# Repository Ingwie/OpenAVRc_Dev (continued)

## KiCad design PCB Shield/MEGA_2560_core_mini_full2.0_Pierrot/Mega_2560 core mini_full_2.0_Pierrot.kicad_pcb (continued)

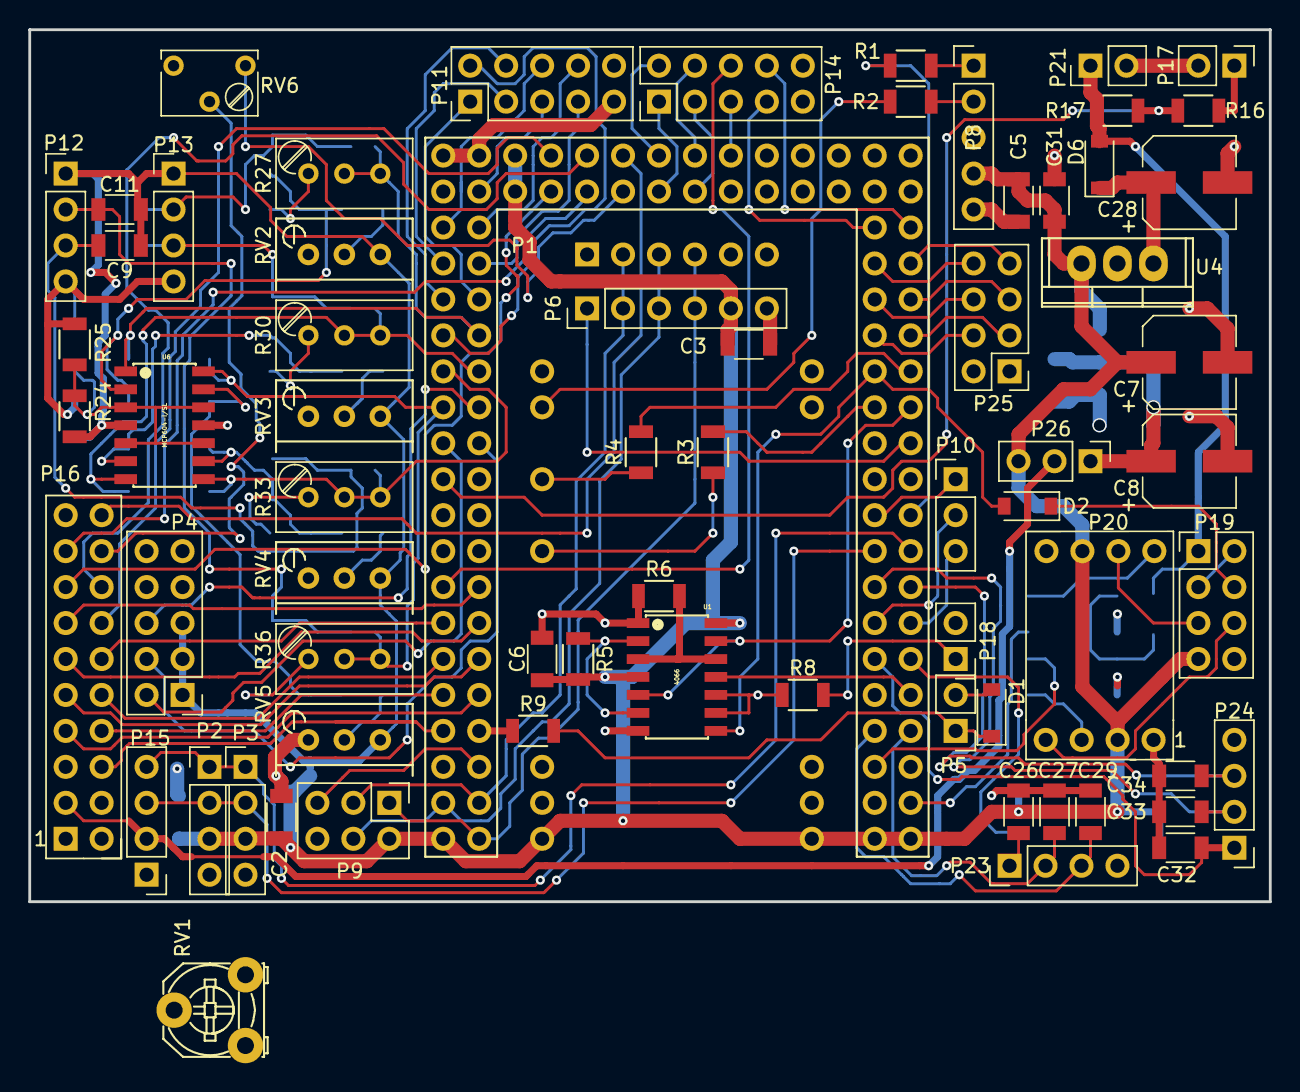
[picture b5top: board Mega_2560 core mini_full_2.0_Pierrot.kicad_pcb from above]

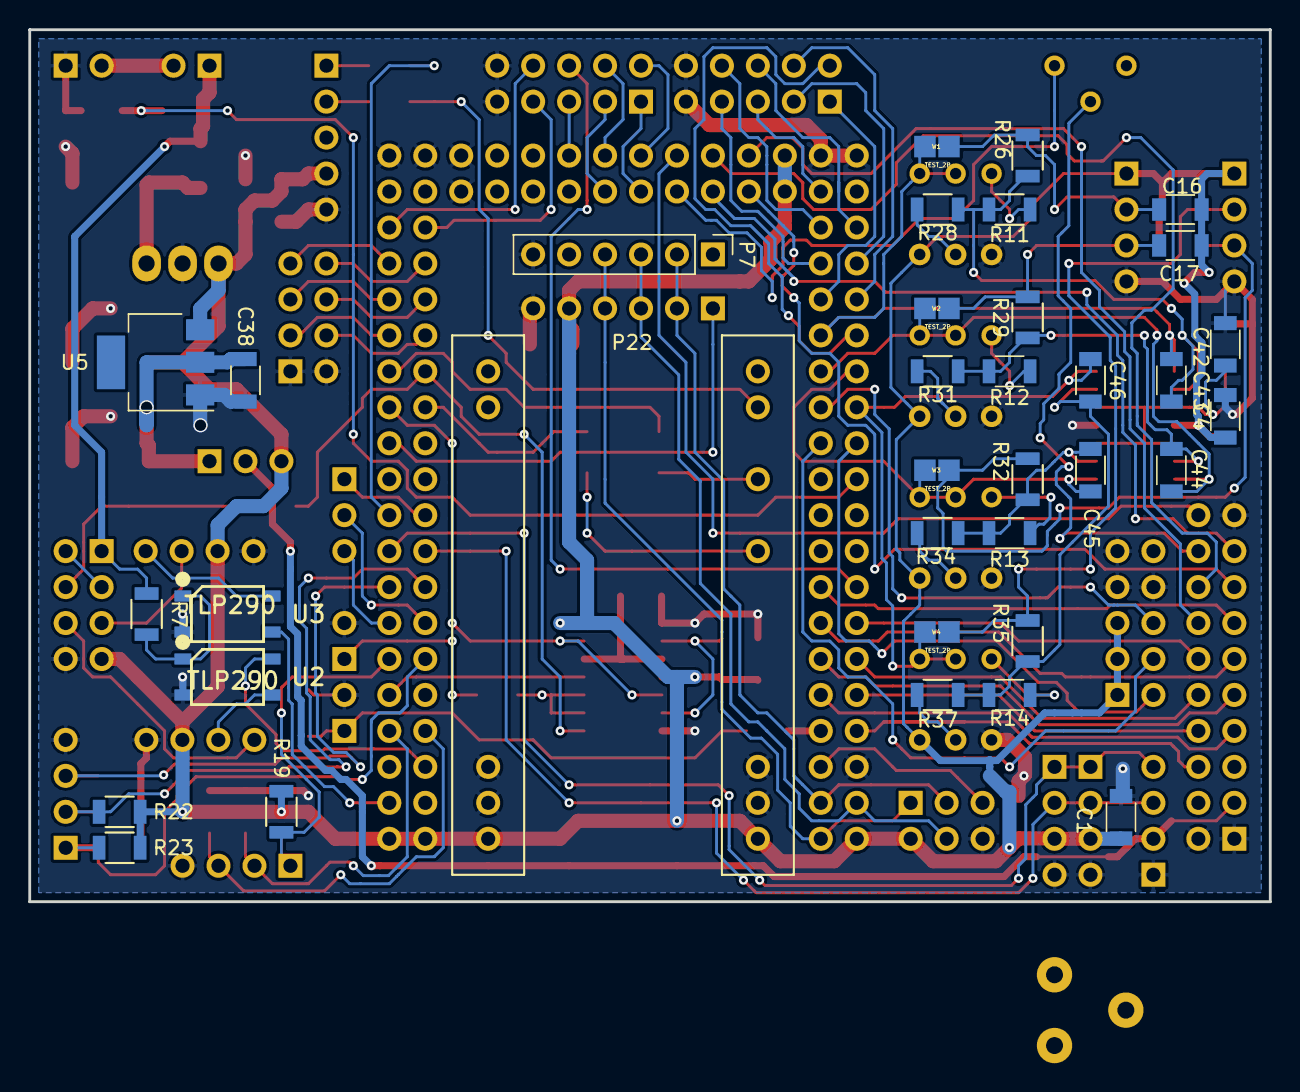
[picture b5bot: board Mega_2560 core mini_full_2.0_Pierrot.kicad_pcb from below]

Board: 2 copper layers, 87.6 x 61.6 mm, 103 parts (35 on the bottom side), 113 nets.

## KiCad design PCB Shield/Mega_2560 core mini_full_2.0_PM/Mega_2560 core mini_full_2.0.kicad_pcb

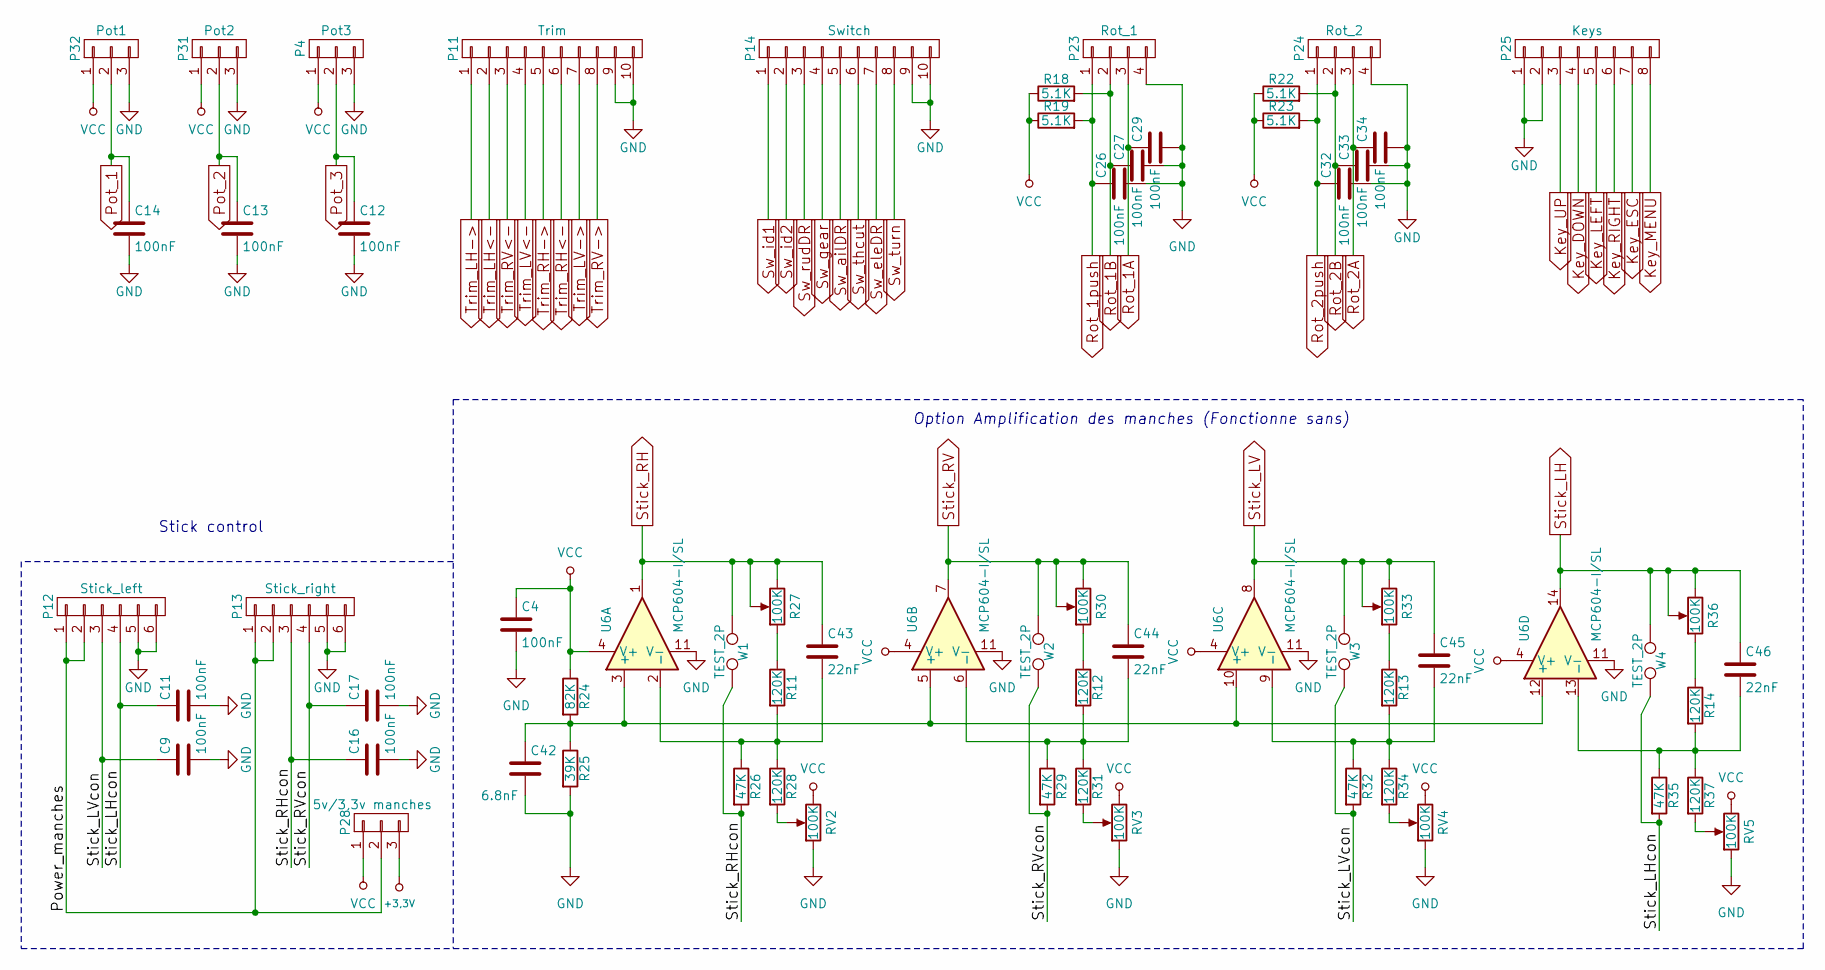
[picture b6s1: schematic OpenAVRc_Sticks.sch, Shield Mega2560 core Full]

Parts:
C4, C9, C11, C12, C13, C14, C16, C17, C26, C27, C29, C32, C33, C34: 100nF; C_1206
C42: 6.8nF; C_1206
C43, C44, C45, C46: 22nF; C_1206
P4: Pot3; Pin_Header_Straight_1x03_Pitch2.54mm
P11: Trim; Pin_Header_Straight_2x05_Pitch2.54mm
P12: Stick_left; Pin_Header_Straight_2x03_Pitch2.54mm
P13: Stick_right; Pin_Header_Straight_1x06_Pitch2.54mm
P14: Switch; Pin_Header_Straight_2x05_Pitch2.54mm
P23: Rot_1; Pin_Header_Straight_1x04_Pitch2.54mm
P24: Rot_2; Pin_Header_Straight_1x04_Pitch2.54mm
P25: Keys; Pin_Header_Straight_2x04_Pitch2.54mm
P28: 5v/3,3v manches; Pin_Header_Straight_1x03_Pitch2.54mm
P31: Pot2; Pin_Header_Straight_1x03_Pitch2.54mm
P32: Pot1; Pin_Header_Straight_1x03_Pitch2.54mm
R11, R12, R13, R14, R28, R31, R34, R37: 120K; R_1206
R18, R19, R22, R23: 5.1K; R_1206
R24: 82K; R_1206
R25: 39K; R_1206
R26, R29, R32, R35: 47K; R_1206
R27, R30, R33, R36: 100K; Potentiometer_Trimmer_Bourns_3296W
RV2, RV3, RV4, RV5: 100K; Potentiometer_Bourns_3296W_3-8Zoll_Inline_ScrewUp
U6: MCP604-I/SL; SOP14
W1, W2, W3, W4: TEST_2P; TESTPT

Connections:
+3.3V: P28.3; also elsewhere on the board
/OpenAVRc_Sticks/Power_manches: P12.1, P12.2, P13.1, P13.2, P28.2
/OpenAVRc_Sticks/Stick_LHcon: C11.1, P12.4, R35.2, W4.2
/OpenAVRc_Sticks/Stick_LVcon: C9.1, P12.3, R32.2, W3.2
/OpenAVRc_Sticks/Stick_RHcon: C16.1, P13.3, R26.2, W1.2
/OpenAVRc_Sticks/Stick_RVcon: C17.1, P13.4, R29.2, W2.2
GND: C4.2, C9.2, C11.2, C12.2, C13.2, C14.2, C16.2, C17.2, C26.2, C27.2, C29.2, C32.2, C33.2, C34.2, C42.2, P4.3, P11.9, P11.10, P12.5, P12.6, P13.5, P13.6, P14.9, P14.10, P23.4, P24.4, P25.1, P25.2, P31.3, P32.3, R25.2, RV2.1, RV3.1, RV4.1, RV5.1, U6.11 (V-); also elsewhere on the board
Key_DOWN: P25.4; also elsewhere on the board
Key_ESC: P25.7; also elsewhere on the board
Key_LEFT: P25.5; also elsewhere on the board
Key_MENU: P25.8; also elsewhere on the board
Key_RIGHT: P25.6; also elsewhere on the board
Key_UP: P25.3; also elsewhere on the board
unnamed: C42.1, R24.2, R25.1, U6.3 (+), U6.5 (+), U6.10 (+), U6.12 (+)
unnamed: C43.2, R11.2, R26.1, R28.1, U6.2 (-)
unnamed: C44.2, R12.2, R29.1, R31.1, U6.6 (-)
unnamed: C45.2, R13.2, R32.1, R34.1, U6.9 (-)
unnamed: C46.2, R14.2, R35.1, R37.1, U6.13 (-)
unnamed: R11.1, R27.1
unnamed: R12.1, R30.1
unnamed: R13.1, R33.1
unnamed: R14.1, R36.1
unnamed: R28.2, RV2.2
unnamed: R31.2, RV3.2
unnamed: R34.2, RV4.2
unnamed: R37.2, RV5.2
Pot_1: C14.1, P32.2; also elsewhere on the board
Pot_2: C13.1, P31.2; also elsewhere on the board
Pot_3: C12.1, P4.2; also elsewhere on the board
Rot_1A: C29.1, P23.3; also elsewhere on the board
Rot_1B: C27.1, P23.2, R18.2; also elsewhere on the board
Rot_1push: C26.1, P23.1, R19.2; also elsewhere on the board
Rot_2A: C34.1, P24.3; also elsewhere on the board
Rot_2B: C33.1, P24.2, R22.2; also elsewhere on the board
Rot_2push: C32.1, P24.1, R23.2; also elsewhere on the board
Stick_LH: C46.1, R36.2, R36.3, U6.14, W4.1; also elsewhere on the board
Stick_LV: C45.1, R33.2, R33.3, U6.8, W3.1; also elsewhere on the board
Stick_RH: C43.1, R27.2, R27.3, U6.1, W1.1; also elsewhere on the board
Stick_RV: C44.1, R30.2, R30.3, U6.7, W2.1; also elsewhere on the board
Sw_ailDR: P14.5; also elsewhere on the board
Sw_eleDR: P14.7; also elsewhere on the board
Sw_gear: P14.4; also elsewhere on the board
Sw_id1: P14.1; also elsewhere on the board
Sw_id2: P14.2; also elsewhere on the board
Sw_rudDR: P14.3; also elsewhere on the board
Sw_thcut: P14.6; also elsewhere on the board
Sw_turn: P14.8; also elsewhere on the board
Trim_LH->: P11.1; also elsewhere on the board
Trim_LH<-: P11.2; also elsewhere on the board
Trim_LV->: P11.7; also elsewhere on the board
Trim_LV<-: P11.4; also elsewhere on the board
Trim_RH->: P11.5; also elsewhere on the board
Trim_RH<-: P11.6; also elsewhere on the board
Trim_RV->: P11.8; also elsewhere on the board
Trim_RV<-: P11.3; also elsewhere on the board
VCC: C4.1, P4.1, P28.1, P31.1, P32.1, R18.1, R19.1, R22.1, R23.1, R24.1, RV2.3, RV3.3, RV4.3, RV5.3, U6.4 (V+); also elsewhere on the board

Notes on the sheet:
Stick control
Option Amplification des manches (Fonctionne sans)

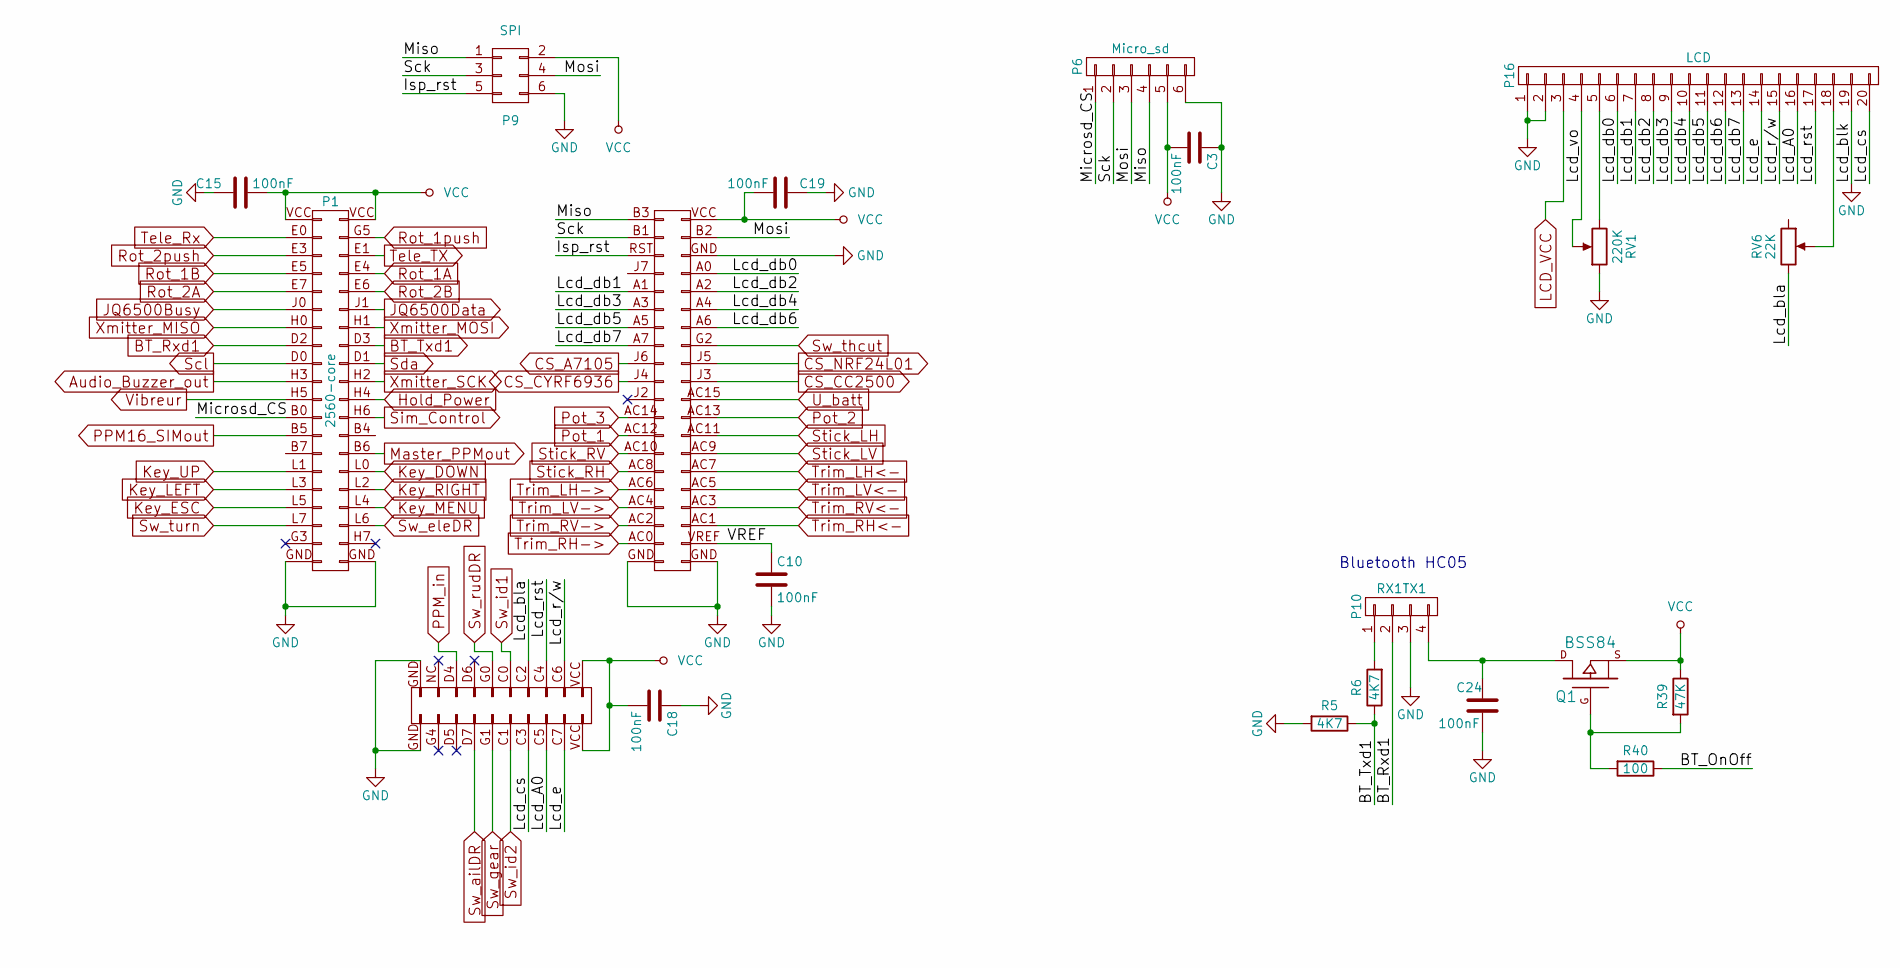
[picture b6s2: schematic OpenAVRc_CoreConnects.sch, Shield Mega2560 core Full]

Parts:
C3, C10, C15, C18, C19, C24: 100nF; C_1206
P1: 2560-core; Connectors-2560-core
P6: Micro_sd; Pin_Header_Straight_1x06_Pitch2.54mm
P9: SPI; Pin_Header_Straight_2x03_Pitch2.54mm
P10: RX1TX1; Pin_Header_Straight_1x04_Pitch2.54mm
P16: LCD; Pin_Header_Straight_2x10_Pitch2.54mm
Q1: BSS84
R5, R6: 4K7; R_1206
R39: 47K; R_1206
R40: 100; R_1206
RV1: 220K; Potentiometer_Trimmer_Bourns_3296W
RV6: 22K; Potentiometer_Trimmer_Bourns_3296W

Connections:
/OpenAVRc_CoreConnects/Isp_rst: P1.RST (P75), P9.5
/OpenAVRc_CoreConnects/Lcd_A0: P1.C5 (P85), P16.16
/OpenAVRc_CoreConnects/Lcd_bla: P1.C2 (P88), RV6.3
/OpenAVRc_CoreConnects/Lcd_cs: P1.C3 (P87), P16.20
/OpenAVRc_CoreConnects/Lcd_db0: P1.A0 (P74), P16.6
/OpenAVRc_CoreConnects/Lcd_db1: P1.A1 (P71), P16.7
/OpenAVRc_CoreConnects/Lcd_db2: P1.A2 (P72), P16.8
/OpenAVRc_CoreConnects/Lcd_db3: P1.A3 (P69), P16.9
/OpenAVRc_CoreConnects/Lcd_db4: P1.A4 (P70), P16.10
/OpenAVRc_CoreConnects/Lcd_db5: P1.A5 (P67), P16.11
/OpenAVRc_CoreConnects/Lcd_db6: P1.A6 (P68), P16.12
/OpenAVRc_CoreConnects/Lcd_db7: P1.A7 (P65), P16.13
/OpenAVRc_CoreConnects/Lcd_e: P1.C7 (P83), P16.14
/OpenAVRc_CoreConnects/Lcd_r/w: P1.C6 (P84), P16.15
/OpenAVRc_CoreConnects/Lcd_rst: P1.C4 (P86), P16.17
/OpenAVRc_CoreConnects/Lcd_vo: P16.4, RV1.2
/OpenAVRc_CoreConnects/Microsd_CS: P1.B0 (P24), P6.1
/OpenAVRc_CoreConnects/Miso: P1.B3 (P79), P6.4, P9.1
/OpenAVRc_CoreConnects/Mosi: P1.B2 (P78), P6.3, P9.4
/OpenAVRc_CoreConnects/Sck: P1.B1 (P77), P6.2, P9.3
/OpenAVRc_CoreConnects/VREF: C10.1, P1.VREF (P44)
Audio_Buzzer_out: P1.H3 (P20); also elsewhere on the board
BT_Rxd1: P1.D2 (P16), P10.2
BT_Txd1: P1.D3 (P15), R5.1, R6.1
CS_A7105: P1.J6 (P63); also elsewhere on the board
CS_CC2500: P1.J3 (P62); also elsewhere on the board
CS_CYRF6936: P1.J4 (P61); also elsewhere on the board
CS_NRF24L01: P1.J5 (P64); also elsewhere on the board
GND: C3.1, C10.2, C15.1, C18.1, C19.1, C24.2, P1.GND (P100), P6.6, P9.6, P10.3, P16.1, P16.2, P16.19, R5.2, RV1.1; also elsewhere on the board
Hold_Power: P1.H4 (P21); also elsewhere on the board
JQ6500Busy: P1.J0 (P12); also elsewhere on the board
JQ6500Data: P1.J1 (P11); also elsewhere on the board
Key_DOWN: P1.L0 (P29); also elsewhere on the board
Key_ESC: P1.L5 (P34); also elsewhere on the board
Key_LEFT: P1.L3 (P32); also elsewhere on the board
Key_MENU: P1.L4 (P33); also elsewhere on the board
Key_RIGHT: P1.L2 (P31); also elsewhere on the board
Key_UP: P1.L1 (P30); also elsewhere on the board
LCD_VCC: P16.3; also elsewhere on the board
Master_PPMout: P1.B6 (P27); also elsewhere on the board
unnamed: C24.1, P10.4, Q1.D
unnamed: P10.1, R6.2
unnamed: P16.5, RV1.3
unnamed: P16.18, RV6.2
unnamed: Q1.G, R39.2, R40.2
PPM16_SIMout: P1.B5 (P26); also elsewhere on the board
PPM_in: P1.D4 (P96); also elsewhere on the board
Pot_1: P1.AC12 (P55); also elsewhere on the board
Pot_2: P1.AC13 (P58); also elsewhere on the board
Pot_3: P1.AC14 (P57); also elsewhere on the board
Rot_1A: P1.E4 (P7); also elsewhere on the board
Rot_1B: P1.E5 (P8); also elsewhere on the board
Rot_1push: P1.G5 (P3); also elsewhere on the board
Rot_2A: P1.E7 (P10); also elsewhere on the board
Rot_2B: P1.E6 (P9); also elsewhere on the board
Rot_2push: P1.E3 (P6); also elsewhere on the board
Scl: P1.D0 (P18); also elsewhere on the board
Sda: P1.D1 (P17); also elsewhere on the board
Sim_Control: P1.H6 (P23); also elsewhere on the board
Stick_LH: P1.AC11 (P56); also elsewhere on the board
Stick_LV: P1.AC9 (P54); also elsewhere on the board
Stick_RH: P1.AC8 (P51); also elsewhere on the board
Stick_RV: P1.AC10 (P53); also elsewhere on the board
Sw_ailDR: P1.D7 (P93); also elsewhere on the board
Sw_eleDR: P1.L6 (P35); also elsewhere on the board
Sw_gear: P1.G1 (P91); also elsewhere on the board
Sw_id1: P1.C0 (P90); also elsewhere on the board
Sw_id2: P1.C1 (P89); also elsewhere on the board
Sw_rudDR: P1.G0 (P92); also elsewhere on the board
Sw_thcut: P1.G2 (P66); also elsewhere on the board
Sw_turn: P1.L7 (P36); also elsewhere on the board
Tele_RX: P1.E0 (P4); also elsewhere on the board
Tele_TX: P1.E1 (P5); also elsewhere on the board
Trim_LH->: P1.AC6 (P49); also elsewhere on the board
Trim_LH<-: P1.AC7 (P52); also elsewhere on the board
Trim_LV->: P1.AC4 (P47); also elsewhere on the board
Trim_LV<-: P1.AC5 (P50); also elsewhere on the board
Trim_RH->: P1.AC0 (P43); also elsewhere on the board
Trim_RH<-: P1.AC1 (P46); also elsewhere on the board
Trim_RV->: P1.AC2 (P45); also elsewhere on the board
Trim_RV<-: P1.AC3 (P48); also elsewhere on the board
U_batt: P1.AC15 (P60); also elsewhere on the board
VCC: C3.2, C15.2, C18.2, C19.2, P1.VCC (P1), P6.5, P9.2, Q1.S, R39.1; also elsewhere on the board
Vibreur: P1.H5 (P22); also elsewhere on the board
Xmitter_MISO: P1.H0 (P14); also elsewhere on the board
Xmitter_MOSI: P1.H1 (P13); also elsewhere on the board
Xmitter_SCK: P1.H2 (P19); also elsewhere on the board

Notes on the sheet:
Bluetooth HC05

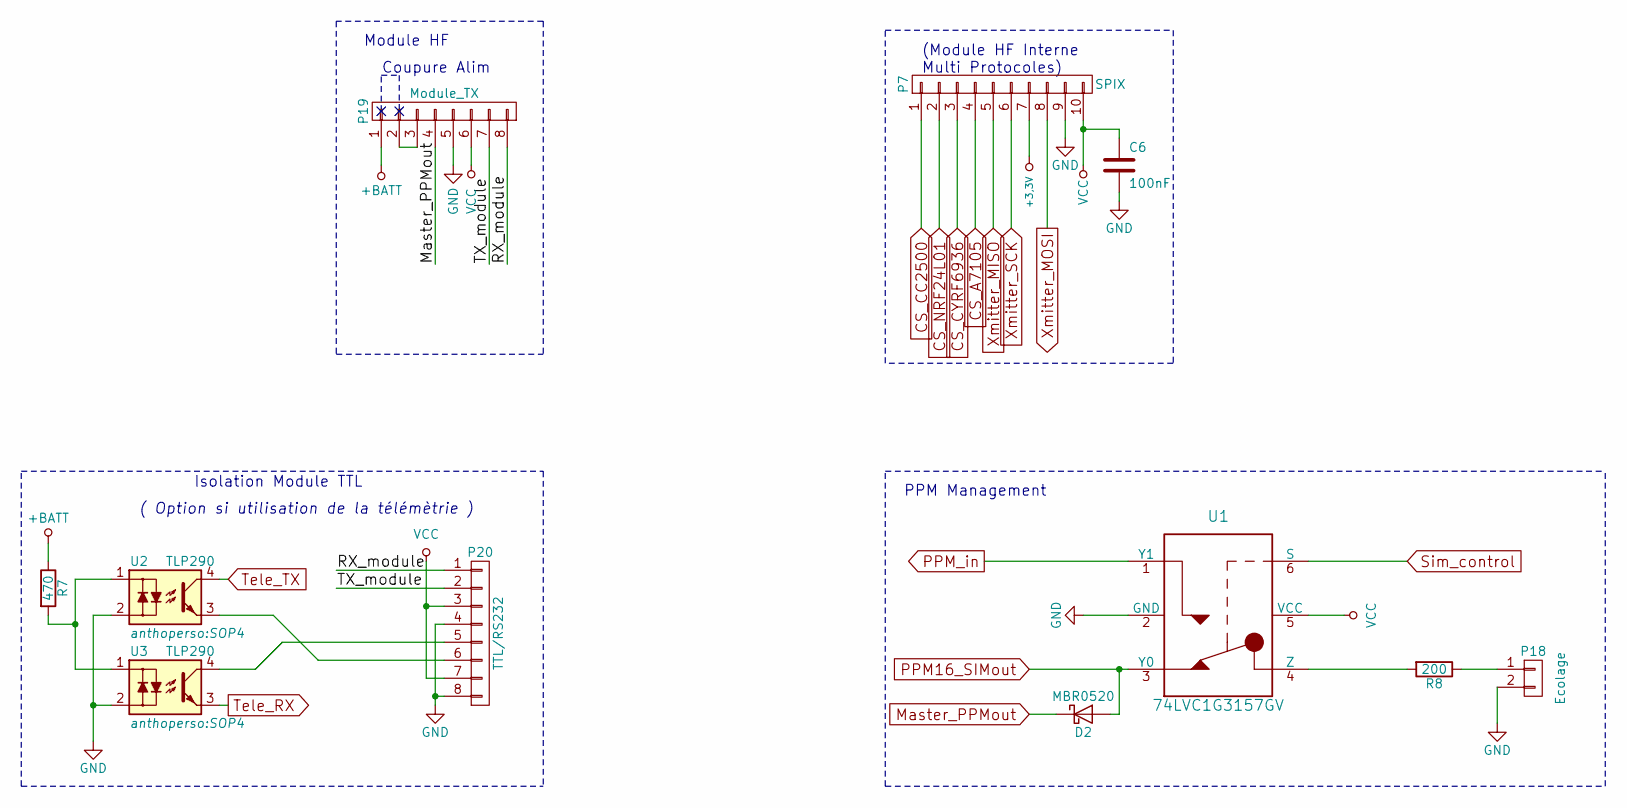
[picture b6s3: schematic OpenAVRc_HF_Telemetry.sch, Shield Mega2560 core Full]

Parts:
C6: 100nF; C_1206
D2: MBR0520; D_SOD-123
P7: SPIX; Pin_Header_Straight_2x05_Pitch2.54mm
P18: Ecolage; Pin_Header_Straight_1x02_Pitch2.54mm
P19: Module_TX; Pin_Header_Straight_2x04_Pitch2.54mm
P20: TTL/RS232; Con_RS232_TTL
R7: 470; R_1206
R8: 200; R_1206
U1: 74LVC1G3157GV; SOT-457
U2, U3: TLP290; SOP4

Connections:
+3.3V: P7.7; also elsewhere on the board
+BATT: P19.1, R7.1; also elsewhere on the board
/OpenAVRc_HF_Telemetry/RX_module: P19.8, P20.1
/OpenAVRc_HF_Telemetry/TX_module: P19.7, P20.2
CS_A7105: P7.4; also elsewhere on the board
CS_CC2500: P7.1; also elsewhere on the board
CS_CYRF6936: P7.3; also elsewhere on the board
CS_NRF24L01: P7.2; also elsewhere on the board
GND: C6.2, P7.9, P18.2, P19.5, P20.4, P20.8, U1.2 (GND), U2.2, U3.2; also elsewhere on the board
Master_PPMout: D2.1 (K), P19.4; also elsewhere on the board
unnamed: P18.1, R8.1
unnamed: P19.2, P19.3
unnamed: P20.5, U3.4
unnamed: P20.6, U2.3
unnamed: R7.2, U2.1, U3.1
unnamed: R8.2, U1.4 (Z)
PPM16_SIMout: D2.2 (A), U1.3 (Y0); also elsewhere on the board
PPM_in: U1.1 (Y1); also elsewhere on the board
Sim_Control: U1.6 (S); also elsewhere on the board
Tele_RX: U3.3; also elsewhere on the board
Tele_TX: U2.4; also elsewhere on the board
VCC: C6.1, P7.10, P19.6, P20.3, P20.7, U1.5 (VCC); also elsewhere on the board
Xmitter_MISO: P7.5; also elsewhere on the board
Xmitter_MOSI: P7.8; also elsewhere on the board
Xmitter_SCK: P7.6; also elsewhere on the board

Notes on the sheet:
Isolation Module TTL
PPM Management
( Option si utilisation de la télémètrie )
Coupure Alim
Module HF
(Module HF Interne Multi Protocoles)

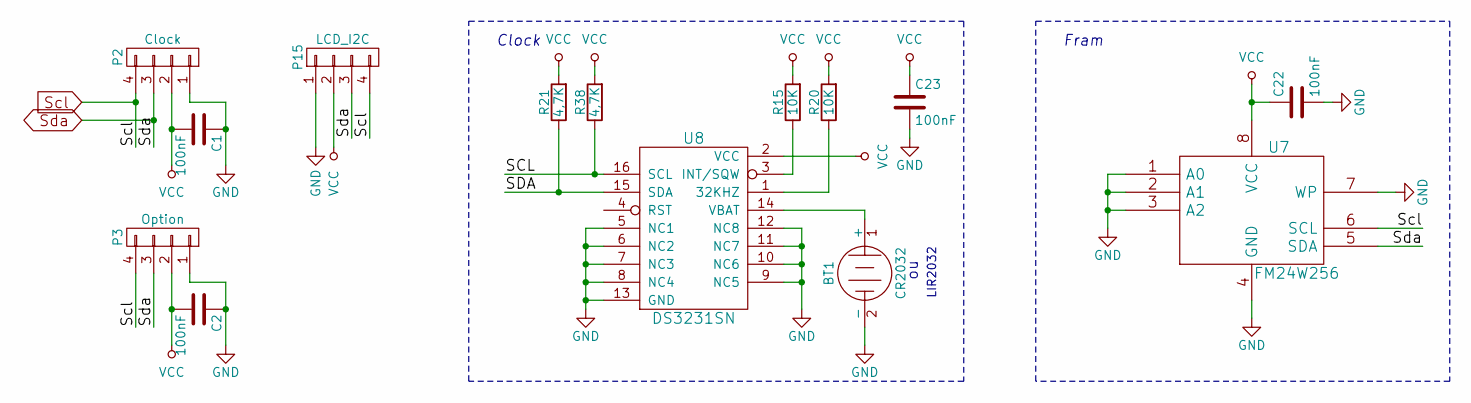
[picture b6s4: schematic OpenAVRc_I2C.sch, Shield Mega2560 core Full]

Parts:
BT1: CR2032; Pin_Header_Straight_1x02_Pitch2.54mm
C1, C2, C22, C23: 100nF; C_1206
P2: Clock; Pin_Header_Straight_1x04_Pitch2.54mm
P3: Option; Pin_Header_Straight_1x04_Pitch2.54mm
P15: LCD_I2C; Pin_Header_Straight_1x04_Pitch2.54mm
R15, R20: 10K; R_1206
R21, R38: 4,7K; R_1206
U7: FM24W256; SOIC-8-FRAM_DI
U8: DS3231SN; SO-16-DS3231

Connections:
GND: BT1.2 (-), C1.1, C2.1, C22.2, C23.2, P2.1, P3.1, P15.1, U7.1 (A0), U7.2 (A1), U7.3 (A2), U7.4 (GND), U7.7 (WP), U8.5 (NC1), U8.6 (NC2), U8.7 (NC3), U8.8 (NC4), U8.9 (NC5), U8.10 (NC6), U8.11 (NC7), U8.12 (NC8), U8.13 (GND); also elsewhere on the board
unnamed: BT1.1 (+), U8.14 (VBAT)
unnamed: R15.1, U8.3 (INT/SQW)
unnamed: R20.1, U8.1 (32KHZ)
Scl: P2.4, P3.4, P15.4, R38.1, U7.6 (SCL), U8.16 (SCL); also elsewhere on the board
Sda: P2.3, P3.3, P15.3, R21.1, U7.5 (SDA), U8.15 (SDA); also elsewhere on the board
VCC: C1.2, C2.2, C22.1, C23.1, P2.2, P3.2, P15.2, R15.2, R20.2, R21.2, R38.2, U7.8 (VCC), U8.2 (VCC); also elsewhere on the board

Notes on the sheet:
Clock
Fram
LIR2032

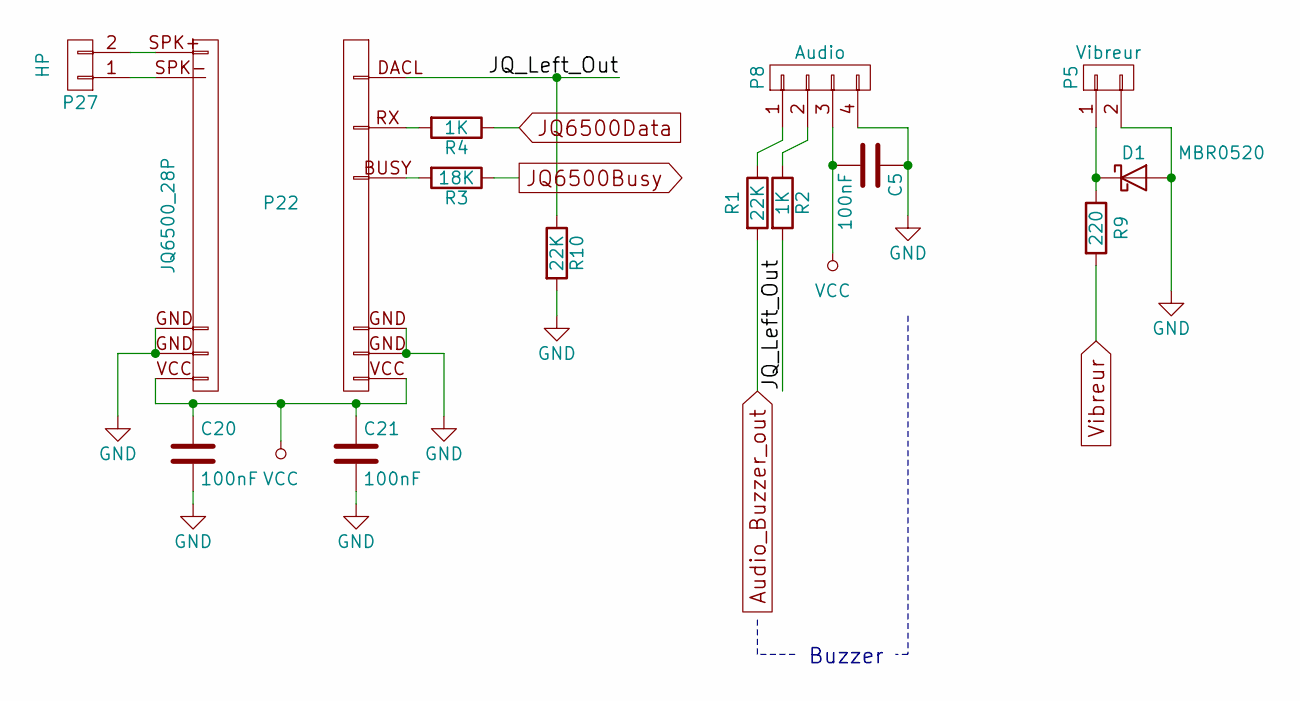
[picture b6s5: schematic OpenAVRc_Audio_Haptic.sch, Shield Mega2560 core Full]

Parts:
C5, C20, C21: 100nF; C_1206
D1: MBR0520; D_SOD-123
P5: Vibreur; Pin_Header_Straight_1x02_Pitch2.54mm
P8: Audio; Pin_Header_Straight_1x04_Pitch2.54mm
P22: JQ6500_28P; connector_mini-JQ6500-28P
P27: HP; Pin_Header_Straight_1x02_Pitch2.54mm
R1, R10: 22K; R_1206
R2, R4: 1K; R_1206
R3: 18K; R_1206
R9: 220; R_1206

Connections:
/OpenAVRc_Audio_Haptic/JQ_Left_Out: P22.DACL (P16), R2.2, R10.1
Audio_Buzzer_out: R1.2; also elsewhere on the board
GND: C5.1, C20.2, C21.2, D1.2 (A), P5.2, P8.4, P22.GND (P12), R10.2; also elsewhere on the board
JQ6500Busy: R3.1; also elsewhere on the board
JQ6500Data: R4.1; also elsewhere on the board
unnamed: D1.1 (K), P5.1, R9.1
unnamed: P8.1, R1.1
unnamed: P8.2, R2.1
unnamed: P22.BUSY (P20), R3.2
unnamed: P22.RX (P18), R4.2
unnamed: P22.SPK+ (P1), P27.2
unnamed: P22.SPK- (P2), P27.1
VCC: C5.2, C20.1, C21.1, P8.3, P22.VCC (P14); also elsewhere on the board
Vibreur: R9.2; also elsewhere on the board

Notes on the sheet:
Buzzer

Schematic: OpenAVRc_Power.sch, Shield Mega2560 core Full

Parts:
C7, C28: 100µF; CP_Elec_6.3x5.3
C8: 47µF; CP_Elec_6.3x5.3
C31, C38: 100nF; C_1206
D3, D4: LL4148; D_SCD80_HandSoldering
D6: MBR0520; D_SOD-123
P17: BATT; Pin_Header_Straight_1x02_Pitch2.54mm
P21: Sw_power; Pin_Header_Straight_1x02_Pitch2.54mm
P26: LCD_Alim; Pin_Header_Straight_1x03_Pitch2.54mm
P29: Sw_On; Pin_Header_Straight_1x02_Pitch2.54mm
P30: MiniDCDC3A
R16: 2.7K; R_1206
R17: 5.1K; R_1206
R41: 33K; R_1206
R42: 2.2K; R_1206
R43: 10K; R_1206
U4: PM5033; PM5033_SIL5
U5: LD1117S33TR; SOT-223

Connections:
+3.3V: C8.1, C38.1, P26.3, U4.5 (3V3), U5.2 (VO1), U5.4 (VO2); also elsewhere on the board
+BATT: D6.2 (A), P21.2, R17.2; also elsewhere on the board
/OpenAVRc_Power/DCDC_IN+: C28.1, D6.1 (K), P30.3, P30.4, R41.1, U4.2 (VIN)
/OpenAVRc_Power/LIPO+: P17.2, P21.1
GND: C7.2, C8.2, C28.2, C31.2, C38.2, P17.1, P30.1, P30.2, P30.7, P30.8, R16.2, R43.2, U4.3 (GND), U5.1 (GND); also elsewhere on the board
Hold_Power: R42.2; also elsewhere on the board
LCD_VCC: P26.2; also elsewhere on the board
unnamed: P29.1, R41.2
unnamed: P29.2, R42.1, R43.1, U4.1 (EN)
U_batt: R16.1, R17.1; also elsewhere on the board
VCC: C7.1, C31.1, P26.1, P30.5, P30.6, U4.4 (5V), U5.3 (VI); also elsewhere on the board

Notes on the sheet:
+3.3V
+5V
Power Management
Option si utilisation du 3.3V dans le montage
Power Switch
DCDC_IN-
Option module DCDC 3A

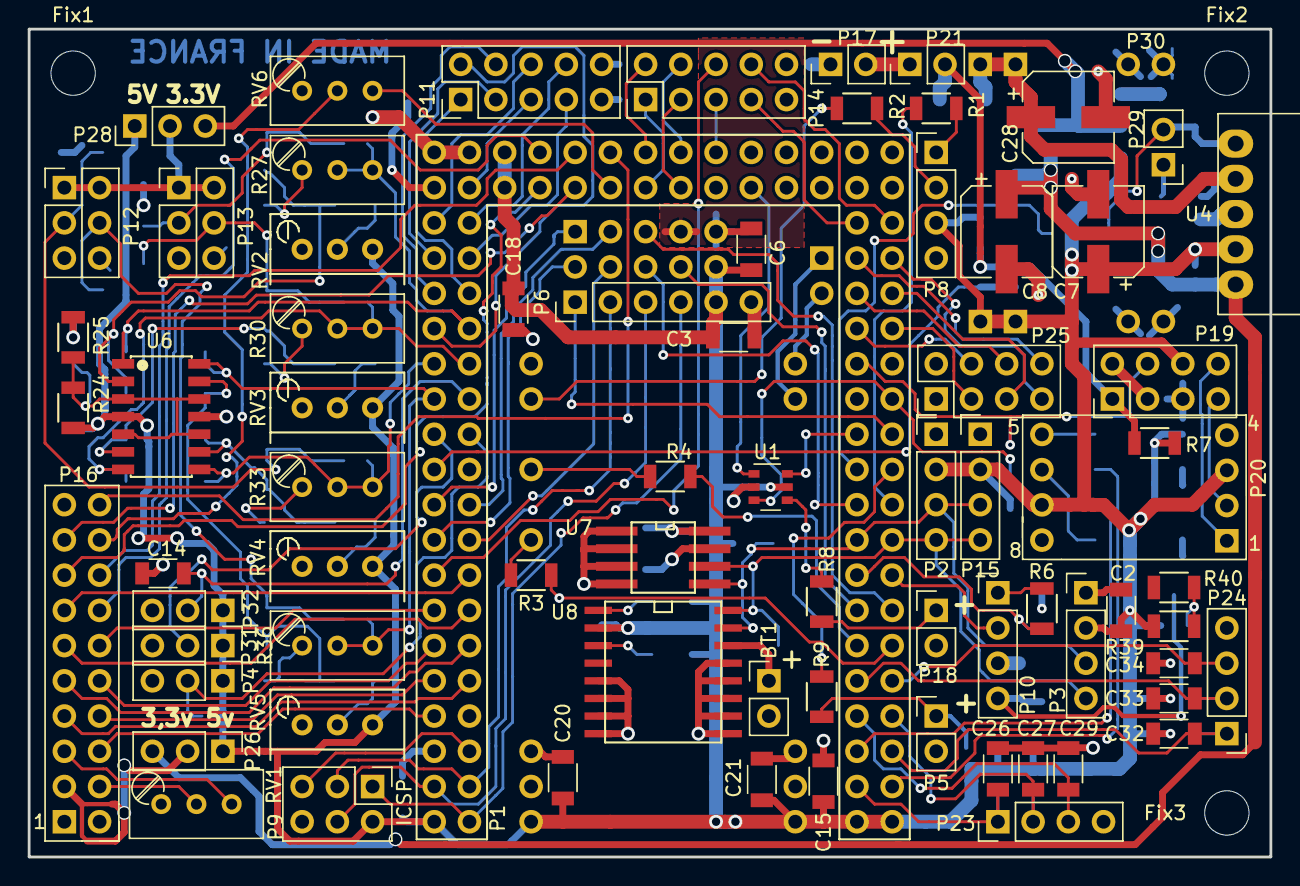
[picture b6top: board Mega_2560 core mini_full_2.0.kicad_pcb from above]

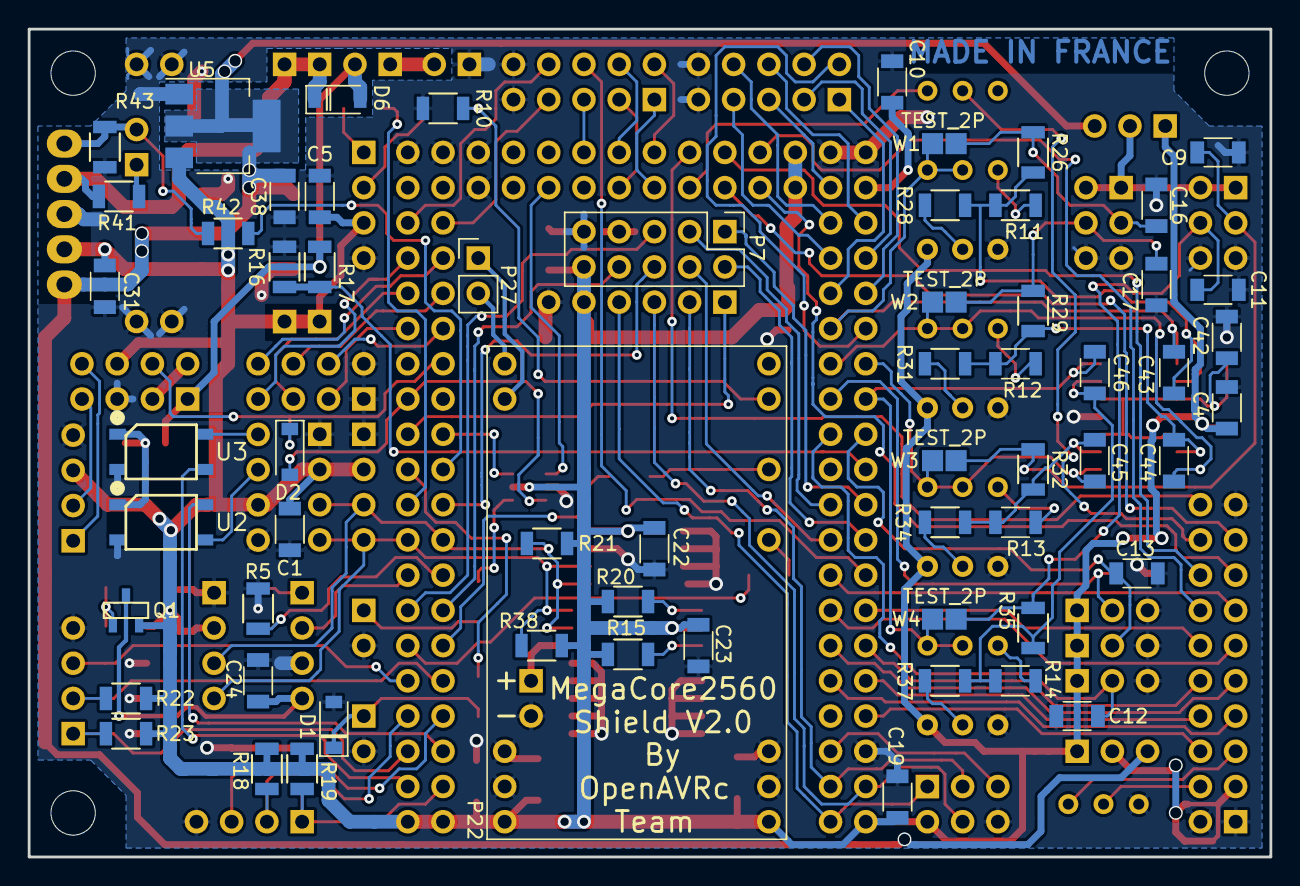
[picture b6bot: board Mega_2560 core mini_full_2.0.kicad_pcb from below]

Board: 2 copper layers, 89.5 x 59.7 mm, 139 parts (62 on the bottom side), 130 nets.

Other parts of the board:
Fix1, Fix2, Fix3: MountingHole_3.2mm_M3

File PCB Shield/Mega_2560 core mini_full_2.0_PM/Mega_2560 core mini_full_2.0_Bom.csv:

"Id";"Référence";"Boîtier";"Quantité";"Désignation";"Fournisseur et réf.";
1;"U4";"Pm5033_sil5";1;"PM5033";;;
2;"R6,R5";"R_1206";2;"4K7";;;
3;"Q1";"SOT-23_MOS_P";1;"BSS84";;;
4;"R40";"R_1206";1;"100";;;
5;"R39,R35,R26,R29,R32";"R_1206";5;"47K";;;
6;"D1,D2,D6";"D_SOD-123";3;"MBR0520";;;
7;"R38,R21";"R_1206";2;"4,7K";;;
8;"U3";"SOP4";1;"TLP290";;;
9;"P16";"Pin_Header_Straight_2x10_Pitch2.54mm";1;"LCD";;;
10;"P1";"Connectors-2560-core";1;"2560-core";;;
11;"P32";"Pin_Header_Straight_1x03_Pitch2.54mm";1;"Pot1";;;
12;"P22";"connector_mini-JQ6500-28P";1;"JQ6500_28P";;;
13;"U1";"SOT-457";1;"74LVC1G3157GV";;;
14;"C24,C23,C22,C21,C20,C19,C18,C15,C14,C13,C12,C10,C1,C16,C29,C38,C34,C33,C32,C31,C27,C26,C17,C11,C9,C5,C3,C2,C4,C6";"C_1206";30;"100nF";;;
15;"P21";"Pin_Header_Straight_1x02_Pitch2.54mm";1;"Sw_power";;;
16;"R8";"R_1206";1;"200";;;
17;"U7";"SOIC-8-FRAM_DI";1;"FM24W256";;;
18;"R20,R15";"R_1206";2;"10K";;;
19;"BT1";"Pin_Header_Straight_1x02_Pitch2.54mm";1;"CR2032";;;
20;"P4";"Pin_Header_Straight_1x03_Pitch2.54mm";1;"Pot3";;;
21;"R10,R1";"R_1206";2;"22K";;;
22;"P31";"Pin_Header_Straight_1x03_Pitch2.54mm";1;"Pot2";;;
23;"P13";"Pin_Header_Straight_2x03_Pitch2.54mm";1;"Stick_right";;;
24;"P12";"Pin_Header_Straight_2x03_Pitch2.54mm";1;"Stick_left";;;
25;"U6";"SOP14";1;"MCP604-I/SL";;;
26;"P17";"Pin_Header_Straight_1x02_Pitch2.54mm";1;"BATT";;;
27;"P24";"Pin_Header_Straight_1x04_Pitch2.54mm";1;"Rot_2";;;
28;"P25";"Pin_Header_Straight_2x04_Pitch2.54mm";1;"Keys";;;
29;"P30";"MiniDCDC3A";1;"MiniDCDC3A";;;
30;"P10";"Pin_Header_Straight_1x04_Pitch2.54mm";1;"RX1TX1";;;
31;"RV6";"Potentiometer_Trimmer_Bourns_3296W";1;"22K";;;
32;"RV1";"Potentiometer_Trimmer_Bourns_3296W";1;"220K";;;
33;"Fix1,Fix3,Fix2";"MountingHole_3.2mm_M3";3;"MountingHole_3.2mm_M3";;;
34;"P27";"Pin_Header_Straight_1x02_Pitch2.54mm";1;"HP";;;
35;"R18,R17,R22,R19,R23";"R_1206";5;"5.1K";;;
36;"R36,R27,R30,R33";"Potentiometer_Trimmer_Bourns_3296W";4;"100K";;;
37;"U5";"SOT-223";1;"LD1117S33TR";;;
38;"C46,C45,C43,C44";"C_1206";4;"22nF";;;
39;"R14,R28,R31,R34,R37,R11,R12,R13";"R_1206";8;"120K";;;
40;"RV4,RV5,RV2,RV3";"Potentiometer_Bourns_3296W_3-8Zoll_Inline_ScrewUp";4;"100K";;;
41;"P15";"Pin_Header_Straight_1x04_Pitch2.54mm";1;"LCD_I2C";;;
42;"P2";"Pin_Header_Straight_1x04_Pitch2.54mm";1;"Clock";;;
43;"P11";"Pin_Header_Straight_2x05_Pitch2.54mm";1;"Trim";;;
44;"P14";"Pin_Header_Straight_2x05_Pitch2.54mm";1;"Switch";;;
45;"R16";"R_1206";1;"2.7K";;;
46;"R2,R4";"R_1206";2;"1K";;;
47;"R3";"R_1206";1;"18K";;;
48;"C42";"C_1206";1;"6.8nF";;;
49;"R24";"R_1206";1;"82K";;;
50;"R25";"R_1206";1;"39K";;;
51;"P28";"Pin_Header_Straight_1x03_Pitch2.54mm";1;"5v/3,3v manches";;;
52;"R7";"R_1206";1;"470";;;
53;"P18";"Pin_Header_Straight_1x02_Pitch2.54mm";1;"Ecolage";;;
54;"P3";"Pin_Header_Straight_1x04_Pitch2.54mm";1;"Option";;;
55;"P5";"Pin_Header_Straight_1x02_Pitch2.54mm";1;"Vibreur";;;
56;"P6";"Pin_Header_Straight_1x06_Pitch2.54mm";1;"Micro_sd";;;
57;"P9";"Pin_Header_Straight_2x03_Pitch2.54mm";1;"SPI";;;
58;"P8";"Pin_Header_Straight_1x04_Pitch2.54mm";1;"Audio";;;
59;"P26";"Pin_Header_Straight_1x03_Pitch2.54mm";1;"LCD_Alim";;;
60;"P23";"Pin_Header_Straight_1x04_Pitch2.54mm";1;"Rot_1";;;
61;"W1,W2,W3,W4";"TESTPT";4;"TEST_2P";;;
62;"R9";"R_1206";1;"220";;;
63;"P19";"Pin_Header_Straight_2x04_Pitch2.54mm";1;"Module_TX";;;
64;"C28,C7";"CP_Elec_6.3x5.3";2;"100µF";;;
65;"C8";"CP_Elec_6.3x5.3";1;"47µF";;;
66;"P20";"Con_RS232_TTL";1;"TTL/RS232";;;
67;"U2";"SOP4";1;"TLP290";;;
68;"U8";"SO-16-DS3231";1;"DS3231SN";;;
69;"D4,D3";"D_SCD80_HandSoldering";2;"LL4148";;;
70;"P7";"Pin_Header_Straight_2x05_Pitch2.54mm";1;"SPIX";;;
